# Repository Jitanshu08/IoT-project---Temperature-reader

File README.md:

# IoT-project---Temperature-reader
Designing a PCB to get the data from the sensor and calculating the ADC through the Arduino microcontroller and uploading it to the dedicated Arduino server.

PCB design folder consist of the one layer design and i have also uploaded the 2 layer design as "PCB design 2layer". The values collected from the sensor is also uploaded as sample values first column the ADC count(analogue reading from the sensor) and the second column shows the input voltage that can be converted it into temperature using the datasheet of the sensor you will be using for your work.

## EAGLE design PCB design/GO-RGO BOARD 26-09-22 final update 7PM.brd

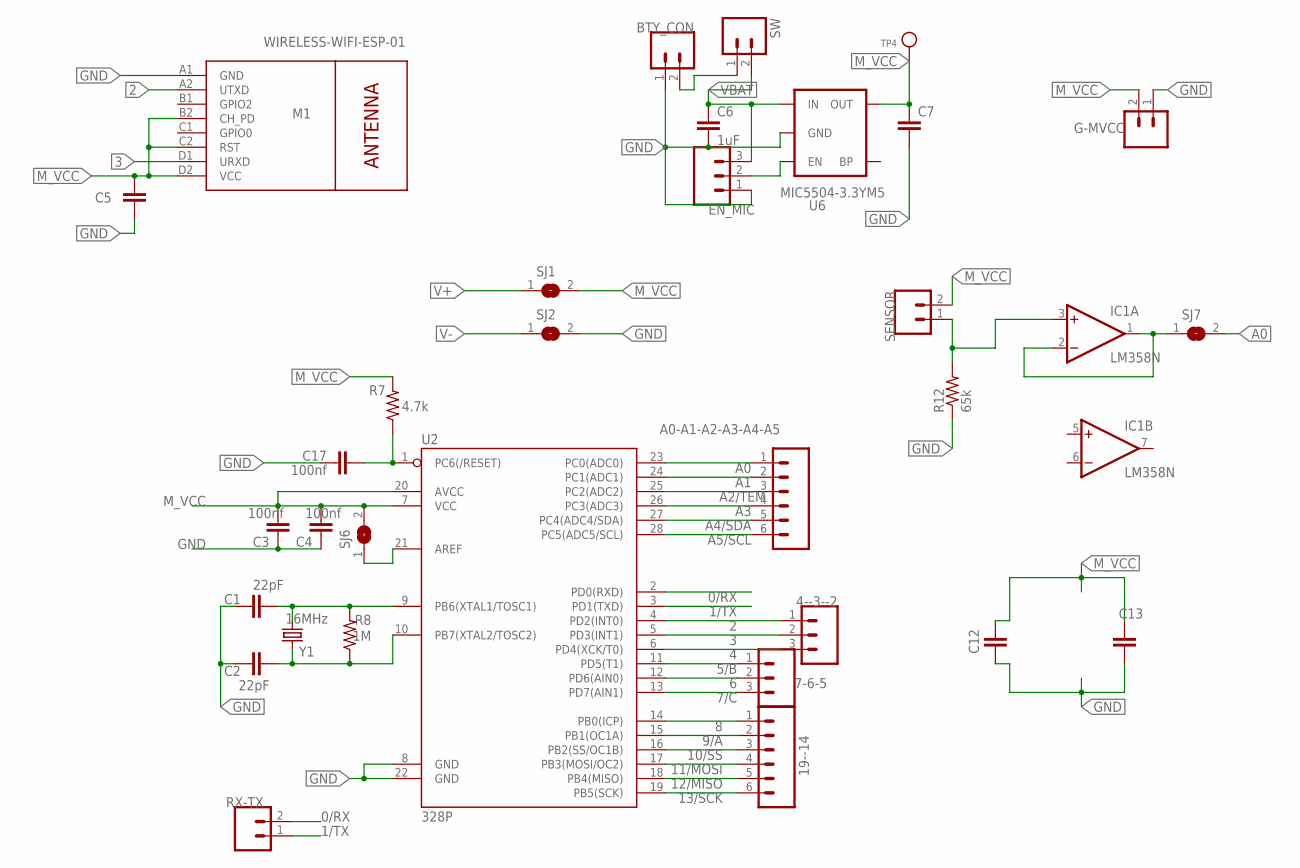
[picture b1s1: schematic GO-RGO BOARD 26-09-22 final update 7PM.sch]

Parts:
4--3--2, 7-6-5: M03PTH; 1X03
19--14: M06SIP; 1X06
A0-A1-A2-A3-A4-A5: M06SIP; 1X06
BTY_CON: M02PTH; 1X02
C1, C2: 22pF; 0805
C3, C4, C5, C12, C13, C17: 100nf; 0805
C6, C7: 1uF; 0805
EN_MIC: M03PTH; 1X03
G-MVCC: M02PTH; 1X02
IC1: LM358N; DIL08
M1: WIRELESS-WIFI-ESP-01
R7: 4.7k; 0805
R8: 1M; 0805
R12: 65k; 0805
RX-TX: M02PTH; 1X02
SENSOR: M02PTH; 1X02
SJ1, SJ2, SJ6, SJ7: SJ
SW: M02PTH; 1X02
TP4: TESTPOINTROUND1MM; TESTPOINT_ROUND_1MM
U2: 328P; DIP28
U6: MIC5504-3.3YM5; SOT23-5
Y1: 16MHz; HC49US

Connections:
0/RX: RX-TX.2, U2.2 (PD0(RXD))
1/TX: RX-TX.1, U2.3 (PD1(TXD))
2: 4--3--2.1, M1.A2 (UTXD), U2.4 (PD2(INT0))
3: 4--3--2.2, M1.D1 (URXD), U2.5 (PD3(INT1))
4: 4--3--2.3, U2.6 (PD4(XCK/T0))
5/B: 7-6-5.1, U2.11 (PD5(T1))
6: 7-6-5.2, U2.12 (PD6(AIN0))
7/C: 7-6-5.3, U2.13 (PD7(AIN1))
8: 19--14.1, U2.14 (PB0(ICP))
9/A: 19--14.2, U2.15 (PB1(OC1A))
10/SS: 19--14.3, U2.16 (PB2(SS/OC1B))
11/MOSI: 19--14.4, U2.17 (PB3(MOSI/OC2))
12/MISO: 19--14.5, U2.18 (PB4(MISO))
13/SCK: 19--14.6, U2.19 (PB5(SCK))
A0: A0-A1-A2-A3-A4-A5.1, SJ7.2, U2.23 (PC0(ADC0))
A1: A0-A1-A2-A3-A4-A5.2, U2.24 (PC1(ADC1))
A2/TEM: A0-A1-A2-A3-A4-A5.3, U2.25 (PC2(ADC2))
A3: A0-A1-A2-A3-A4-A5.4, U2.26 (PC3(ADC3))
A4/SDA: A0-A1-A2-A3-A4-A5.5, U2.27 (PC4(ADC4/SDA))
A5/SCL: A0-A1-A2-A3-A4-A5.6, U2.28 (PC5(ADC5/SCL))
GND: BTY_CON.1, C1.1, C2.1, C3.1, C4.1, C5.1, C6.2, C7.2, C12.1, C13.1, C17.1, EN_MIC.1, G-MVCC.1, M1.A1 (GND), R12.1, SJ2.2, U2.8 (GND), U2.22 (GND), U6.2 (GND)
M_VCC: C3.2, C4.2, C5.2, C7.1, C12.2, C13.2, G-MVCC.2, M1.B2 (CH_PD), M1.C2 (RST), M1.D2 (VCC), R7.2, SENSOR.2, SJ1.2, SJ6.2, TP4.P$1, U2.7 (VCC), U2.20 (AVCC), U6.5 (OUT)
unnamed: BTY_CON.2, SW.1
unnamed: IC1.3 (+IN), R12.2, SENSOR.1
unnamed: EN_MIC.2, U6.3 (EN)
unnamed: C17.2, R7.1, U2.1 (PC6(/RESET))
unnamed: SJ6.1, U2.21 (AREF)
unnamed: IC1.1 (OUT), IC1.2 (-IN), SJ7.1
unnamed: C1.2, R8.2, U2.9 (PB6(XTAL1/TOSC1)), Y1.2
unnamed: C2.2, R8.1, U2.10 (PB7(XTAL2/TOSC2)), Y1.1
V+: IC1.8 (V+), SJ1.1
V-: IC1.4 (V-), SJ2.1
VBAT: C6.1, EN_MIC.3, SW.2, U6.1 (IN)

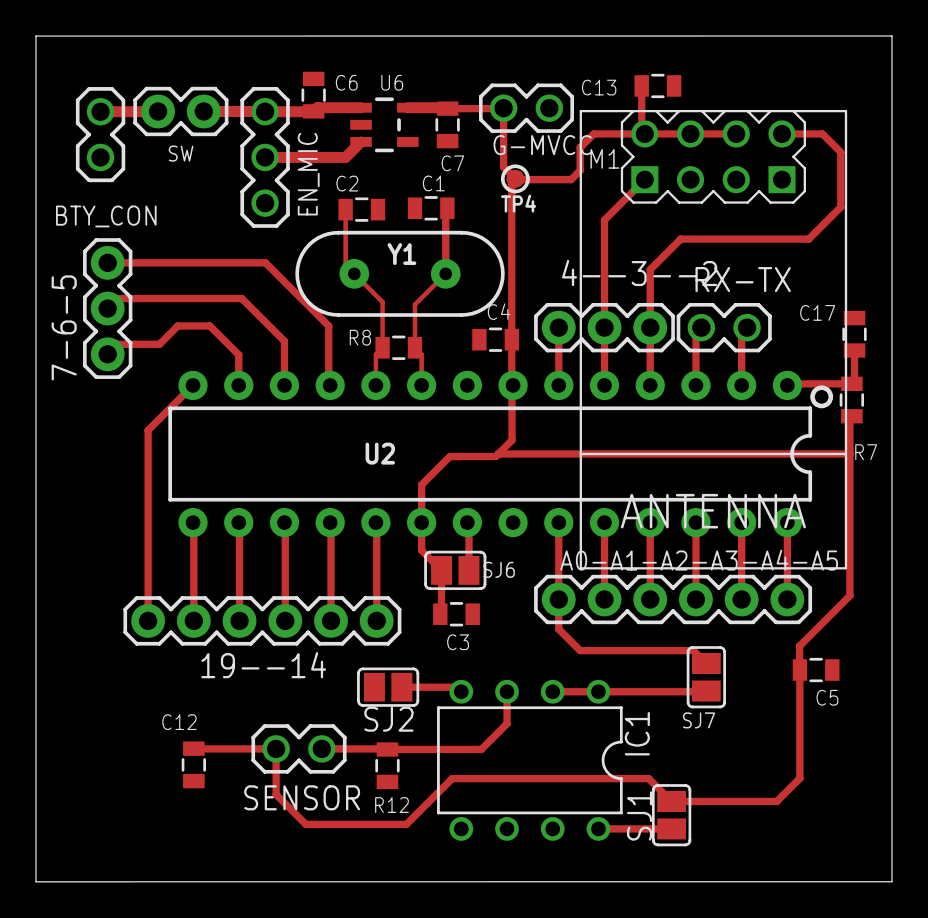
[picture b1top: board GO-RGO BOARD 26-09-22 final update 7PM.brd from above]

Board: 2 copper layers, 47.6 x 47.0 mm, 33 parts (0 on the bottom side), 33 nets.

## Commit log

2023-07-07 Arduino uno code for reading temperature
2023-07-07 PCB design for arduino
    It's in Eagle software, and the tracing is done on the first layer, but I am also uploading two layers of tracing PCB design
2023-07-07 Matlab code for plotting graph
    This code will plot the graph between ADC count VS input voltage
2023-07-07 Sample Values
    this is an sample values which i got from the PCB I made to collect the data from the temperature sensor
2023-07-07 README.md

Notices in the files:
parts and their libraries:
SparkFun-Connectors1: Licensing: Creative Commons ShareAlike 4.0 International - https://creativecommons.org/licenses/by-sa/4.0
SparkFun-Capacitors: Licensing: CC v3.0 Share-Alike You are welcome to use this library for commercial purposes.
